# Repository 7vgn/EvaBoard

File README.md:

# EvaBoard evolved
## An Evaluation Board for the ATmega644(A)

This is an evaluation board for the ATmega644(A). It is inspired by (and compatible with) the [evaluation board](https://www.embedded.rwth-aachen.de/doku.php?id=lehre:atmegaevaboard)  used in the lab course "Praktikum Systemprogrammierung" in the computer science curriculum at RWTH Aachen. 

This repository contains:

- A richly illustrated [Guide Book](Guide/EvaBoardGuide.pdf) with everything you need to know to build and use the board
- A [KiCAD project](KiCAD/) with the [Schematic](KiCAD/Schematic.pdf) and a PCB layout, ready to be manufactured
- The [bill of materials](BOM/BOM.pdf)
- Drivers for the [LCD](Drivers/LCD/) and the [serial port](Drivers/Serial/)
- [Test code](Tests/) for testing and debugging the board

Related projects:

- [SRAM Board evolved](https://github.com/7vgn/SRAMBoard/), an add-on board with 128kBytes of additional SRAM
- [AD/DA Board evolved](https://github.com/7vgn/ADDABoard/), an add-on board for experimenting with analogue-digital and digital-analogue conversion

> [!NOTE]
> I have a small number of PCBs left over. If you're a student wanting to build the board, [contact me](https://github.com/7vgn/EvaBoard/discussions).

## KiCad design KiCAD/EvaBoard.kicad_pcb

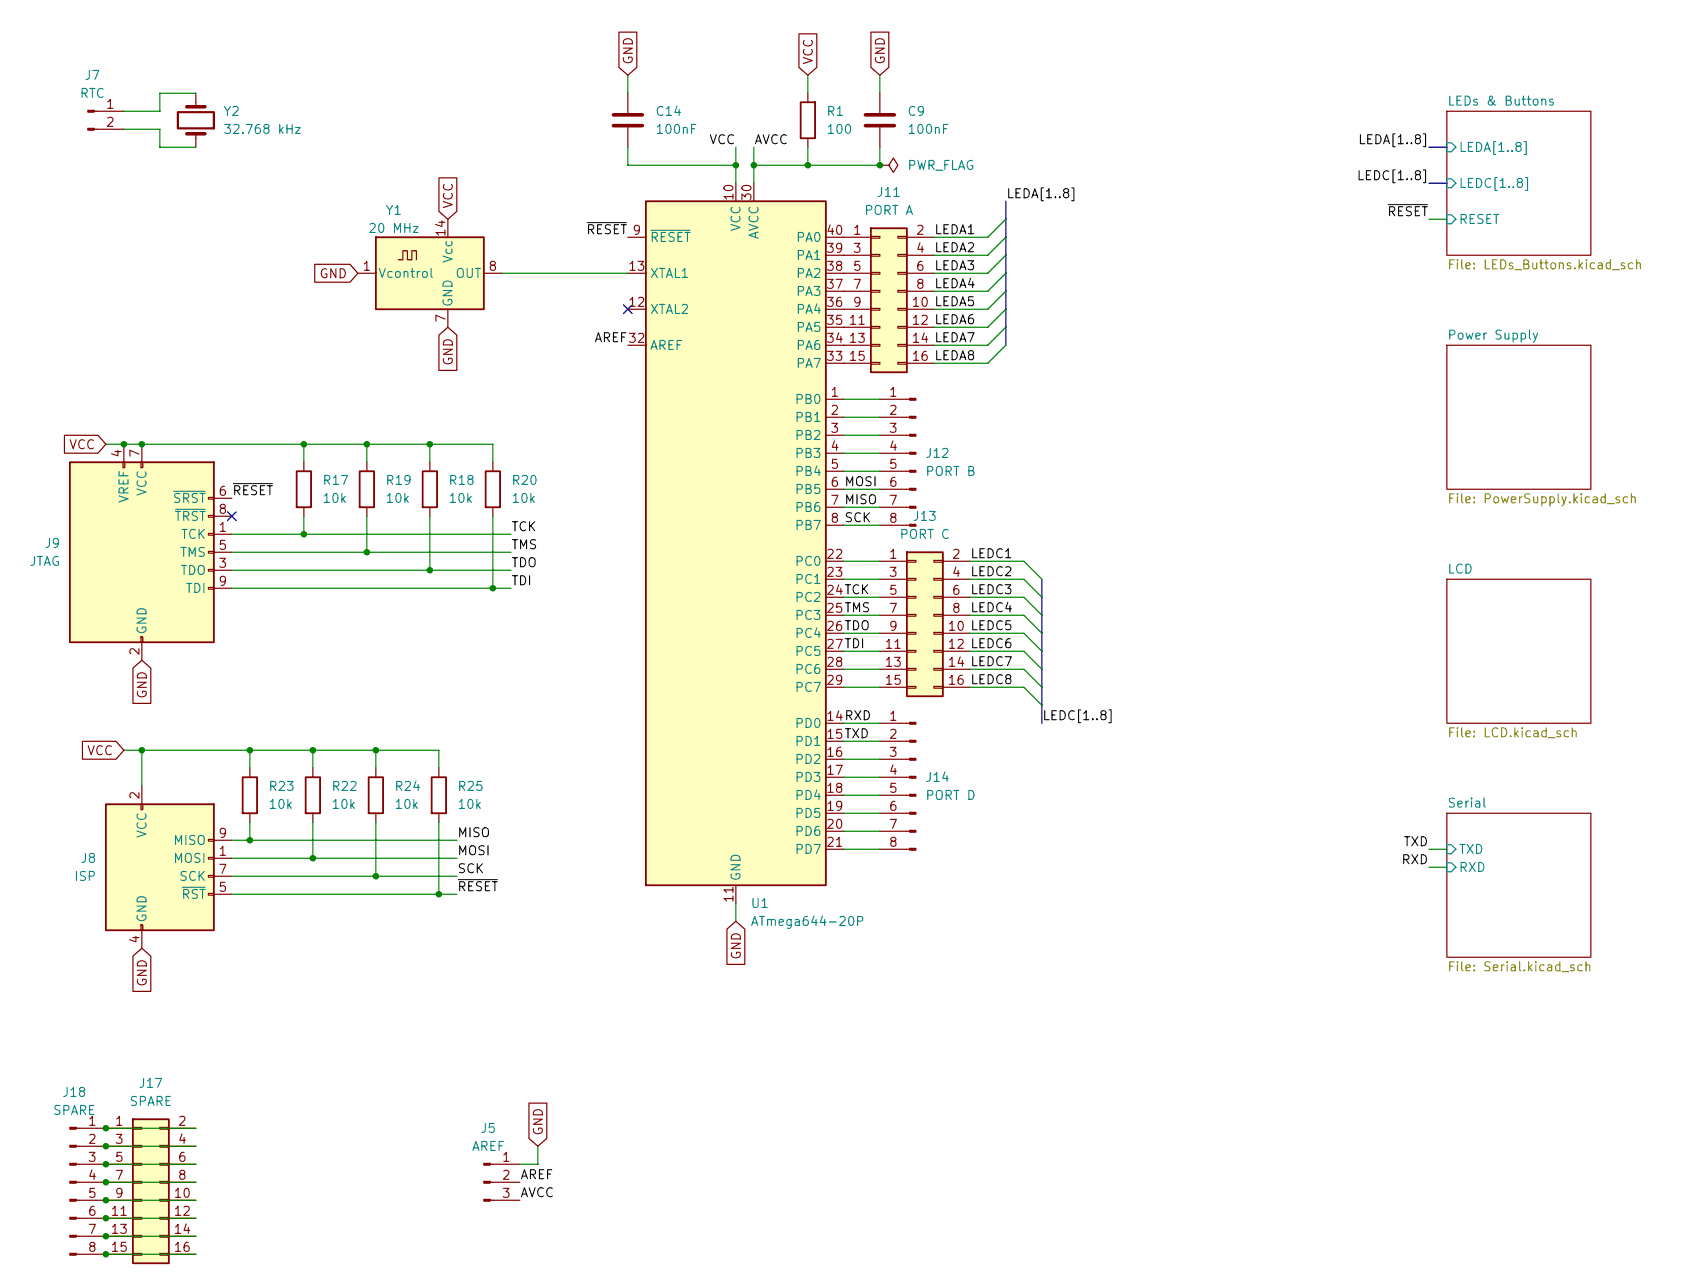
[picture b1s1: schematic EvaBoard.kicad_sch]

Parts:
C9, C14: 100nF; C_Disc_D5.0mm_W2.5mm_P5.00mm
J5: AREF; PinHeader_1x03_P2.54mm_Vertical
J7: RTC; PinHeader_1x02_P2.54mm_Vertical
J8: ISP; IDC-Header_2x05_P2.54mm_Vertical
J9: JTAG; IDC-Header_2x05_P2.54mm_Vertical
J11: PORT A; PinHeader_2x08_P2.54mm_Vertical
J12: PORT B; PinHeader_1x08_P2.54mm_Vertical
J13: PORT C; PinHeader_2x08_P2.54mm_Vertical
J14: PORT D; PinHeader_1x08_P2.54mm_Vertical
J17: SPARE; PinHeader_2x08_P2.54mm_Vertical
J18: SPARE; PinHeader_1x08_P2.54mm_Vertical
R1: 100; R_Axial_DIN0207_L6.3mm_D2.5mm_P10.16mm_Horizontal
R17, R18, R19, R20, R22, R23, R24, R25: 10k; R_Axial_DIN0207_L6.3mm_D2.5mm_P10.16mm_Horizontal
U1: ATmega644-20P; DIP-40_W15.24mm
Y1: 20 MHz; DIP-14_W7.62mm
Y2: 32.768 kHz; Crystal_C38-LF_D3.0mm_L8.0mm_Horizontal

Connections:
/AREF: J5.2, U1.32 (AREF)
/AVCC: C9.1, J5.3, R1.1, U1.30 (AVCC)
/LEDA1: J11.2; also elsewhere on the board
/LEDA2: J11.4; also elsewhere on the board
/LEDA3: J11.6; also elsewhere on the board
/LEDA4: J11.8; also elsewhere on the board
/LEDA5: J11.10; also elsewhere on the board
/LEDA6: J11.12; also elsewhere on the board
/LEDA7: J11.14; also elsewhere on the board
/LEDA8: J11.16; also elsewhere on the board
/LEDC1: J13.2; also elsewhere on the board
/LEDC2: J13.4; also elsewhere on the board
/LEDC3: J13.6; also elsewhere on the board
/LEDC4: J13.8; also elsewhere on the board
/LEDC5: J13.10; also elsewhere on the board
/LEDC6: J13.12; also elsewhere on the board
/LEDC7: J13.14; also elsewhere on the board
/LEDC8: J13.16; also elsewhere on the board
/MISO: J8.9 (MISO), J12.7, R23.2, U1.7 (PB6)
/MOSI: J8.1 (MOSI), J12.6, R22.2, U1.6 (PB5)
/RXD: J14.1, U1.14 (PD0); also elsewhere on the board
/SCK: J8.7 (SCK), J12.8, R24.2, U1.8 (PB7)
/TCK: J9.1 (TCK), J13.5, R17.2, U1.24 (PC2)
/TDI: J9.9 (TDI), J13.11, R20.2, U1.27 (PC5)
/TDO: J9.3 (TDO), J13.9, R18.2, U1.26 (PC4)
/TMS: J9.5 (TMS), J13.7, R19.2, U1.25 (PC3)
/TXD: J14.2, U1.15 (PD1); also elsewhere on the board
/~RESET: J8.5 (~RST), J9.6 (~SRST), R25.2, U1.9 (~RESET); also elsewhere on the board
GND: C9.2, C14.1, J5.1, J8.4 (GND), J8.6 (GND), J8.8 (GND), J8.10 (GND), J9.2 (GND), J9.10 (GND), U1.11 (GND), U1.31 (GND), Y1.1 (Vcontrol), Y1.7 (GND); also elsewhere on the board
unnamed: J7.1, Y2.2
unnamed: J7.2, Y2.1
unnamed: J11.1, U1.40 (PA0)
unnamed: J11.3, U1.39 (PA1)
unnamed: J11.5, U1.38 (PA2)
unnamed: J11.7, U1.37 (PA3)
unnamed: J11.9, U1.36 (PA4)
unnamed: J11.11, U1.35 (PA5)
unnamed: J11.13, U1.34 (PA6)
unnamed: J11.15, U1.33 (PA7)
unnamed: J12.1, U1.1 (PB0)
unnamed: J12.2, U1.2 (PB1)
unnamed: J12.3, U1.3 (PB2)
unnamed: J12.4, U1.4 (PB3)
unnamed: J12.5, U1.5 (PB4)
unnamed: J13.1, U1.22 (PC0)
unnamed: J13.3, U1.23 (PC1)
unnamed: J13.13, U1.28 (PC6)
unnamed: J13.15, U1.29 (PC7)
unnamed: J14.3, U1.16 (PD2)
unnamed: J14.4, U1.17 (PD3)
unnamed: J14.5, U1.18 (PD4)
unnamed: J14.6, U1.19 (PD5)
unnamed: J14.7, U1.20 (PD6)
unnamed: J14.8, U1.21 (PD7)
unnamed: J17.1, J17.2, J18.1
unnamed: J17.3, J17.4, J18.2
unnamed: J17.5, J17.6, J18.3
unnamed: J17.7, J17.8, J18.4
unnamed: J17.9, J17.10, J18.5
unnamed: J17.11, J17.12, J18.6
unnamed: J17.13, J17.14, J18.7
unnamed: J17.15, J17.16, J18.8
unnamed: U1.13 (XTAL1), Y1.8 (OUT)
VCC: C14.2, J8.2 (VCC), J9.4 (VREF), J9.7 (VCC), R1.2, R17.1, R18.1, R19.1, R20.1, R22.1, R23.1, R24.1, R25.1, U1.10 (VCC), Y1.14 (Vcc); also elsewhere on the board

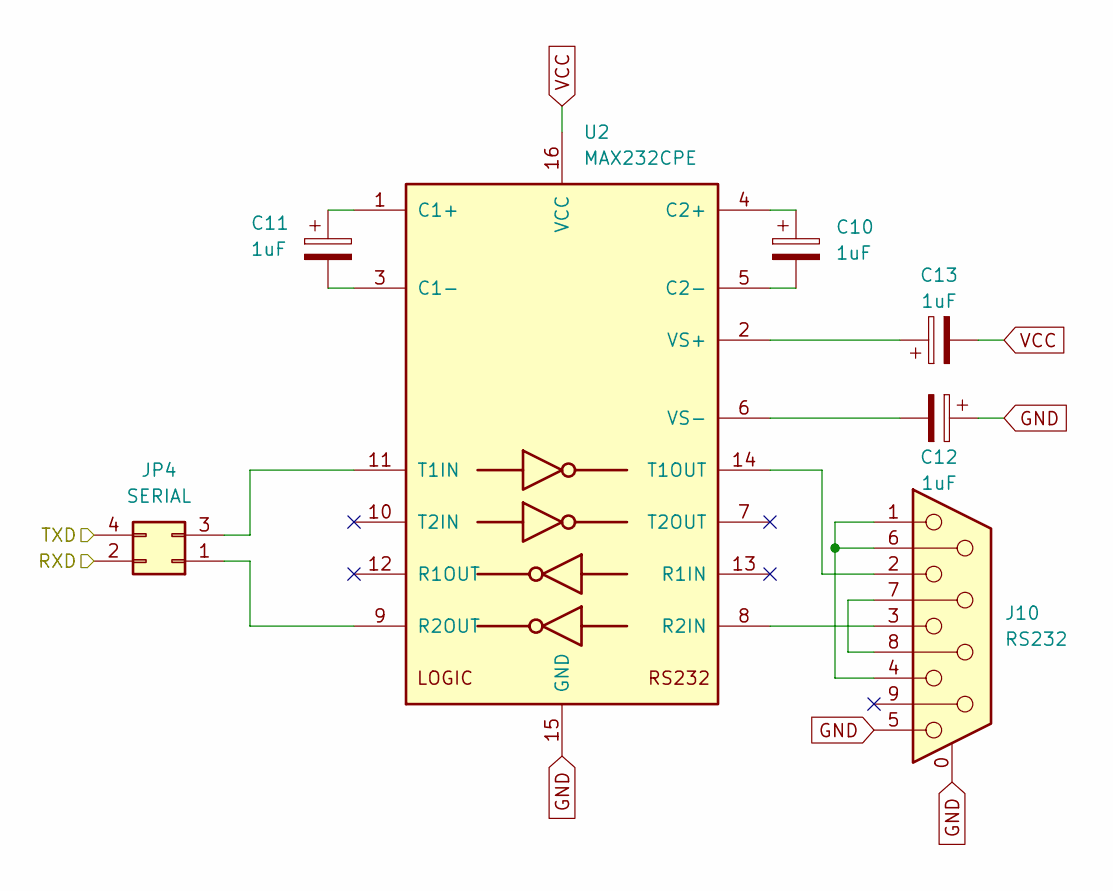
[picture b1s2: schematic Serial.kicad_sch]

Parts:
C10, C11, C12, C13: 1uF; CP_Radial_D5.0mm_P2.00mm
J10: RS232; DSUB-9_Female_Horizontal_P2.77x2.84mm_EdgePinOffset7.70mm_H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
JP4: SERIAL; PinHeader_2x02_P2.54mm_Vertical
U2: MAX232CPE; DIP-16_W7.62mm

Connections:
/RXD: JP4.2; also elsewhere on the board
/TXD: JP4.4; also elsewhere on the board
GND: C12.1, J10.0 (PAD), J10.5, U2.15 (GND); also elsewhere on the board
unnamed: C10.1, U2.4 (C2+)
unnamed: C10.2, U2.5 (C2-)
unnamed: C11.1, U2.1 (C1+)
unnamed: C11.2, U2.3 (C1-)
unnamed: C12.2, U2.6 (VS-)
unnamed: C13.1, U2.2 (VS+)
unnamed: J10.1, J10.4, J10.6
unnamed: J10.2, U2.14 (T1OUT)
unnamed: J10.3, U2.8 (R2IN)
unnamed: J10.7, J10.8
unnamed: JP4.1, U2.9 (R2OUT)
unnamed: JP4.3, U2.11 (T1IN)
VCC: C13.2, U2.16 (VCC); also elsewhere on the board

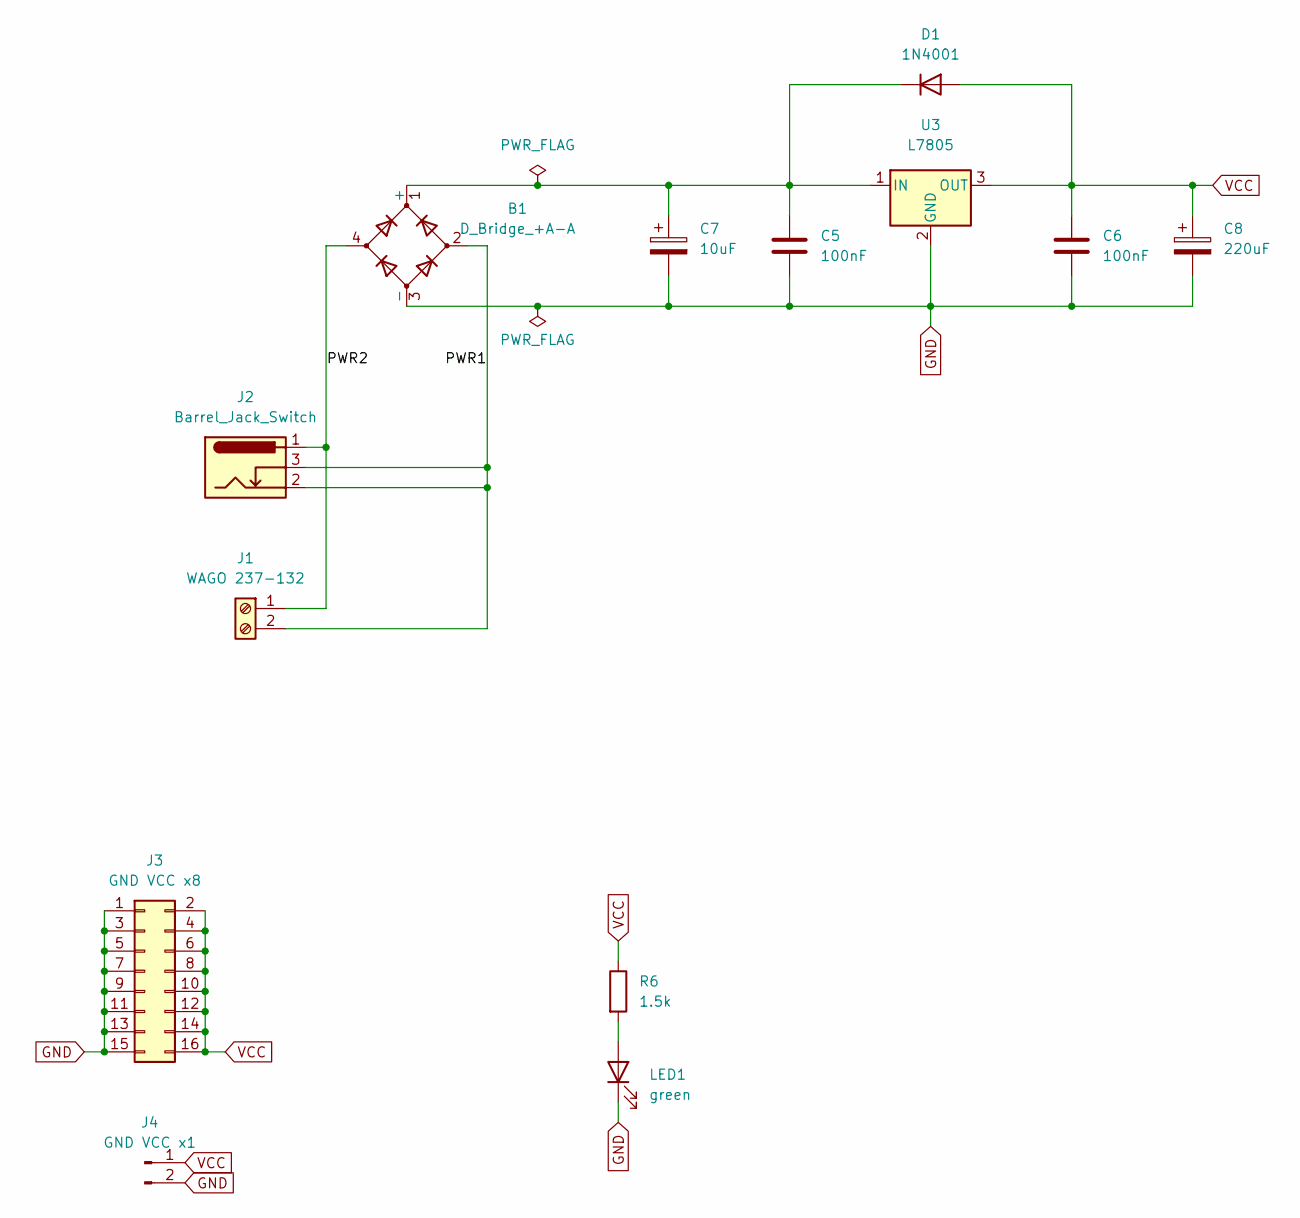
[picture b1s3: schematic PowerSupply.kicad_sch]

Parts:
B1: D_Bridge_+A-A; Diode_Bridge_Round_D8.9mm
C5, C6: 100nF; C_Disc_D5.0mm_W2.5mm_P5.00mm
C7: 10uF; CP_Axial_L18.0mm_D6.5mm_P25.00mm_Horizontal
C8: 220uF; CP_Radial_D10.0mm_P5.00mm
D1: 1N4001; D_DO-41_SOD81_P10.16mm_Horizontal
J1: WAGO 237-132; TerminalBlock_RND_205-00001_1x02_P5.00mm_Horizontal
J2: Barrel_Jack_Switch; BarrelJack_Horizontal
J3: GND VCC x8; PinHeader_2x08_P2.54mm_Vertical
J4: GND VCC x1; PinHeader_1x02_P2.54mm_Vertical
LED1: green; LED_D3.0mm
R6: 1.5k; R_Axial_DIN0207_L6.3mm_D2.5mm_P10.16mm_Horizontal
U3: L7805; TO-220-3_Horizontal_TabDown

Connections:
/Power Supply/PWR1: B1.2, J1.2, J2.2, J2.3
/Power Supply/PWR2: B1.4, J1.1, J2.1
GND: B1.3 (-), C5.2, C6.2, C7.2, C8.2, J3.1, J3.3, J3.5, J3.7, J3.9, J3.11, J3.13, J3.15, J4.2, LED1.1 (K), U3.2 (GND); also elsewhere on the board
unnamed: B1.1 (+), C5.1, C7.1, D1.1 (K), U3.1 (IN)
unnamed: LED1.2 (A), R6.2
VCC: C6.1, C8.1, D1.2 (A), J3.2, J3.4, J3.6, J3.8, J3.10, J3.12, J3.14, J3.16, J4.1, R6.1, U3.3 (OUT); also elsewhere on the board

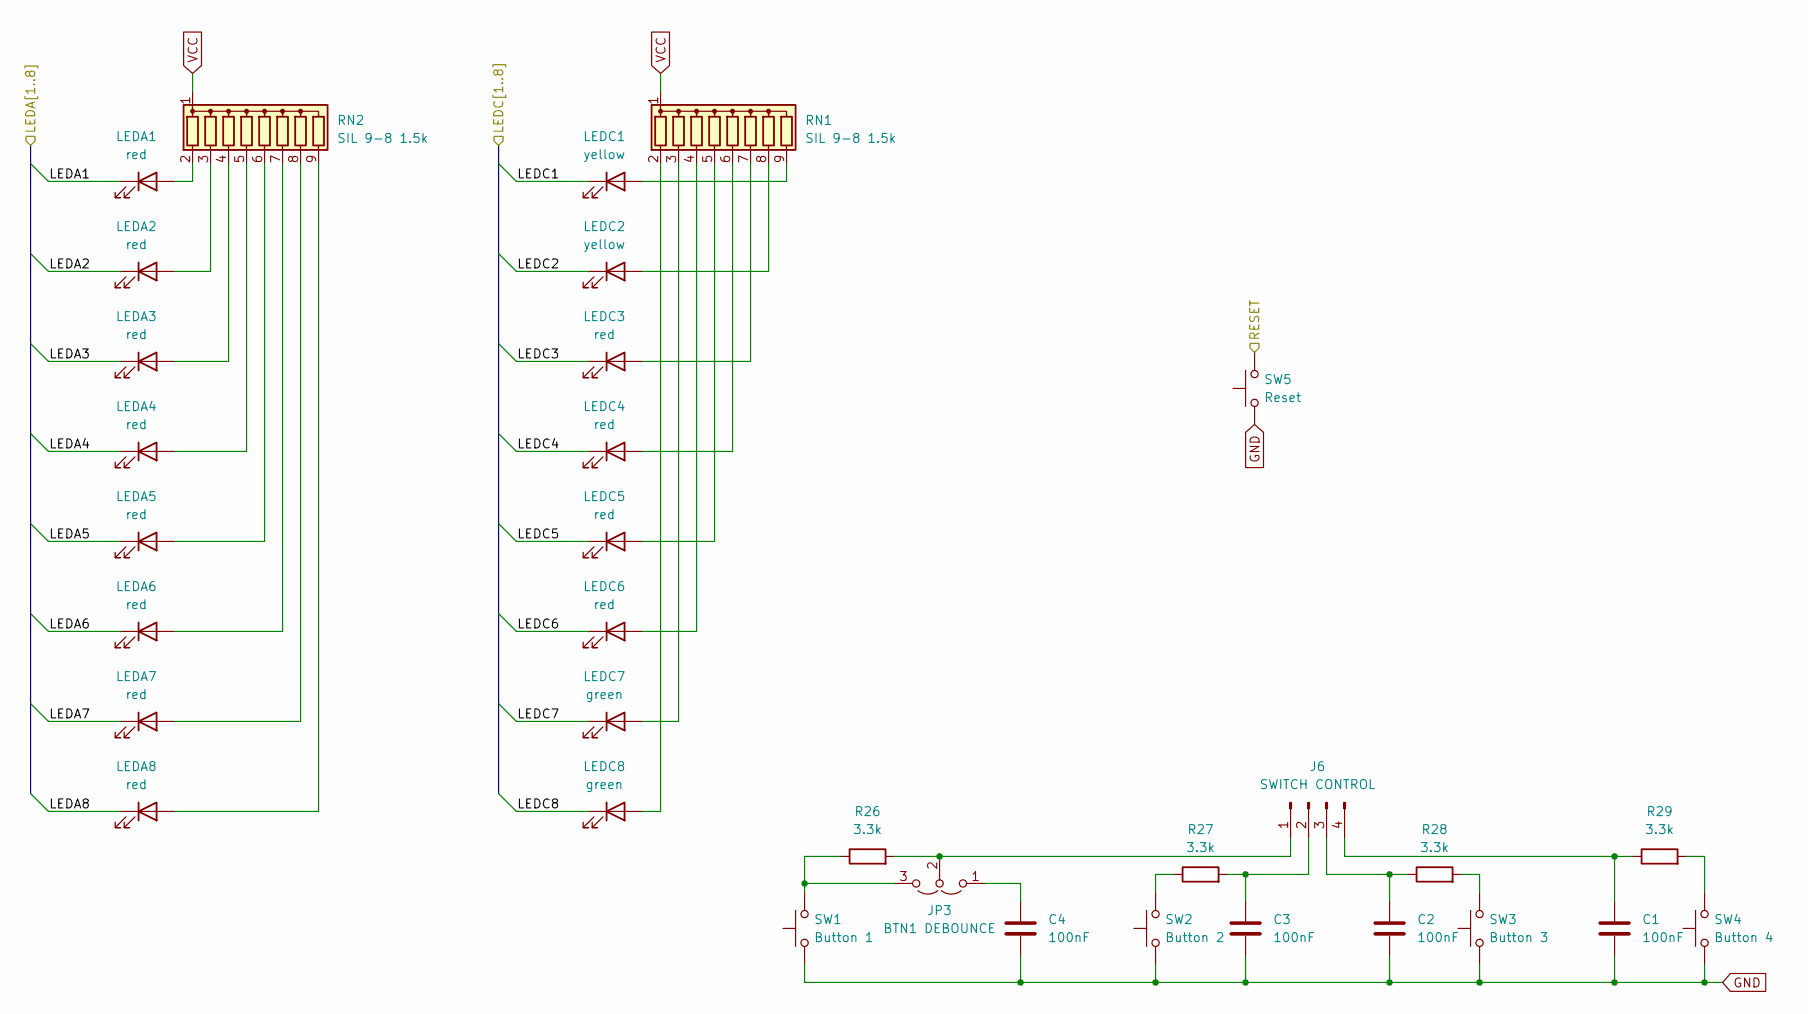
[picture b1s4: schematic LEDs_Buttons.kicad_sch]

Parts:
C1, C2, C3, C4: 100nF; C_Disc_D5.0mm_W2.5mm_P5.00mm
J6: SWITCH CONTROL; PinHeader_1x04_P2.54mm_Vertical
JP3: BTN1 DEBOUNCE; PinHeader_1x03_P2.54mm_Vertical
LEDA1, LEDA2, LEDA3, LEDA4, LEDA5, LEDA6, LEDA7, LEDA8: red; LED_D3.0mm
LEDC1, LEDC2: yellow; LED_D3.0mm
LEDC3, LEDC4, LEDC5, LEDC6: red; LED_D3.0mm
LEDC7, LEDC8: green; LED_D3.0mm
R26, R27, R28, R29: 3.3k; R_Axial_DIN0207_L6.3mm_D2.5mm_P10.16mm_Horizontal
RN1, RN2: SIL 9-8 1.5k; R_Array_SIP9
SW1: Button 1; SW_PUSH_6mm
SW2: Button 2; SW_PUSH_6mm
SW3: Button 3; SW_PUSH_6mm
SW4: Button 4; SW_PUSH_6mm
SW5: Reset; SW_PUSH_6mm

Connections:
/LEDA1: LEDA1.1 (K); also elsewhere on the board
/LEDA2: LEDA2.1 (K); also elsewhere on the board
/LEDA3: LEDA3.1 (K); also elsewhere on the board
/LEDA4: LEDA4.1 (K); also elsewhere on the board
/LEDA5: LEDA5.1 (K); also elsewhere on the board
/LEDA6: LEDA6.1 (K); also elsewhere on the board
/LEDA7: LEDA7.1 (K); also elsewhere on the board
/LEDA8: LEDA8.1 (K); also elsewhere on the board
/LEDC1: LEDC1.1 (K); also elsewhere on the board
/LEDC2: LEDC2.1 (K); also elsewhere on the board
/LEDC3: LEDC3.1 (K); also elsewhere on the board
/LEDC4: LEDC4.1 (K); also elsewhere on the board
/LEDC5: LEDC5.1 (K); also elsewhere on the board
/LEDC6: LEDC6.1 (K); also elsewhere on the board
/LEDC7: LEDC7.1 (K); also elsewhere on the board
/LEDC8: LEDC8.1 (K); also elsewhere on the board
/~RESET: SW5.2; also elsewhere on the board
GND: C1.1, C2.1, C3.1, C4.2, SW1.1, SW2.1, SW3.1, SW4.1, SW5.1; also elsewhere on the board
unnamed: C1.2, J6.4, R29.1
unnamed: C2.2, J6.3, R28.1
unnamed: C3.2, J6.2, R27.2
unnamed: C4.1, JP3.1 (A)
unnamed: J6.1, JP3.2 (C), R26.2
unnamed: JP3.3 (B), R26.1, SW1.2
unnamed: LEDA1.2 (A), RN2.2 (R1)
unnamed: LEDA2.2 (A), RN2.3 (R2)
unnamed: LEDA3.2 (A), RN2.4 (R3)
unnamed: LEDA4.2 (A), RN2.5 (R4)
unnamed: LEDA5.2 (A), RN2.6 (R5)
unnamed: LEDA6.2 (A), RN2.7 (R6)
unnamed: LEDA7.2 (A), RN2.8 (R7)
unnamed: LEDA8.2 (A), RN2.9 (R8)
unnamed: LEDC1.2 (A), RN1.9 (R8)
unnamed: LEDC2.2 (A), RN1.8 (R7)
unnamed: LEDC3.2 (A), RN1.7 (R6)
unnamed: LEDC4.2 (A), RN1.6 (R5)
unnamed: LEDC5.2 (A), RN1.5 (R4)
unnamed: LEDC6.2 (A), RN1.4 (R3)
unnamed: LEDC7.2 (A), RN1.3 (R2)
unnamed: LEDC8.2 (A), RN1.2 (R1)
unnamed: R27.1, SW2.2
unnamed: R28.2, SW3.2
unnamed: R29.2, SW4.2
VCC: RN1.1 (common), RN2.1 (common); also elsewhere on the board

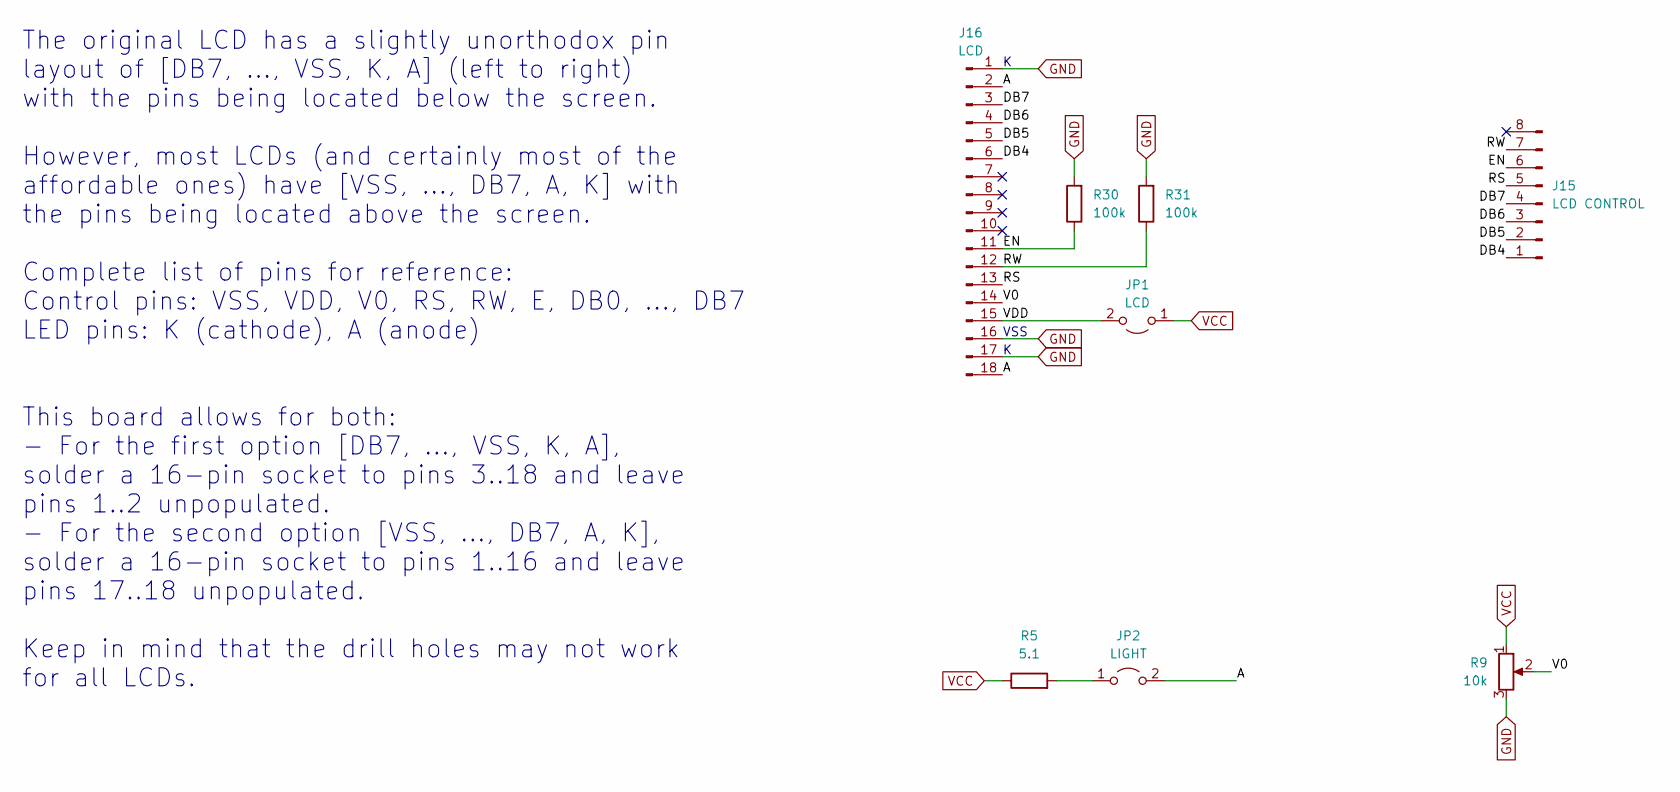
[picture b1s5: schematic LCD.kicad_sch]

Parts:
J15: LCD CONTROL; PinHeader_1x08_P2.54mm_Vertical
J16: LCD; PinSocket_1x18_P2.54mm_Vertical
JP1: LCD; PinHeader_1x02_P2.54mm_Vertical
JP2: LIGHT; PinHeader_1x02_P2.54mm_Vertical
R5: 5.1; R_Axial_DIN0207_L6.3mm_D2.5mm_P10.16mm_Horizontal
R9: 10k; Potentiometer_Bourns_3386P_Vertical
R30, R31: 100k; R_Axial_DIN0207_L6.3mm_D2.5mm_P10.16mm_Horizontal

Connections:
/LCD/A: J16.2, J16.18, JP2.2 (B)
/LCD/DB4: J15.1, J16.6
/LCD/DB5: J15.2, J16.5
/LCD/DB6: J15.3, J16.4
/LCD/DB7: J15.4, J16.3
/LCD/EN: J15.6, J16.11, R30.1
/LCD/RS: J15.5, J16.13
/LCD/RW: J15.7, J16.12, R31.1
/LCD/V0: J16.14, R9.2
/LCD/VDD: J16.15, JP1.2 (B)
GND: J16.1, J16.16, J16.17, R9.3, R30.2, R31.2; also elsewhere on the board
unnamed: JP2.1 (A), R5.2
VCC: JP1.1 (A), R5.1, R9.1; also elsewhere on the board

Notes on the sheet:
The original LCD has a slightly unorthodox pin layout of [DB7, ..., VSS, K, A] (left to right) with the pins being located below the screen. However, most LCDs (and certainly most of the affordable ones) have [VSS, ..., DB7, A, K] with the pins being located above the screen. Complete list of pins 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
VSS

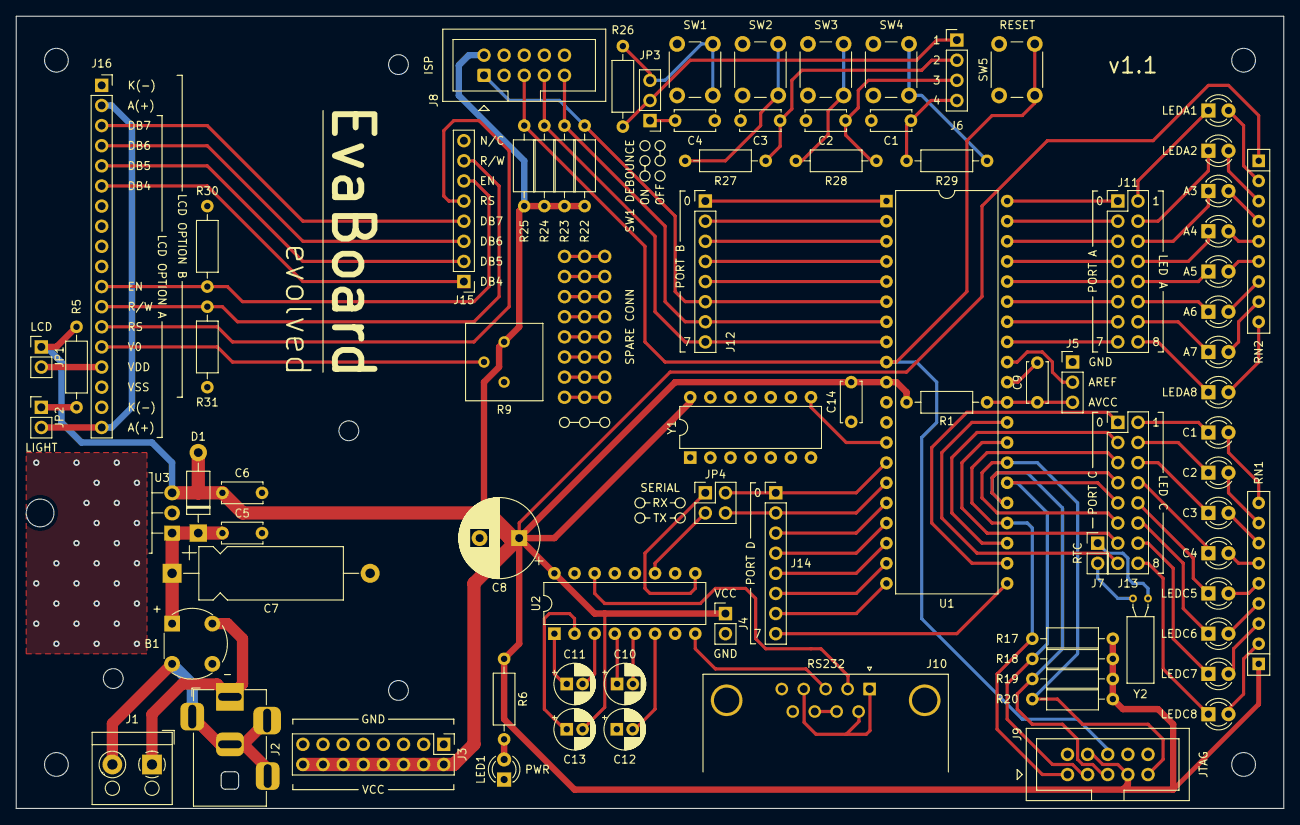
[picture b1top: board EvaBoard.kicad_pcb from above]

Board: 2 copper layers, 160.0 x 100.0 mm, 85 parts (0 on the bottom side), 116 nets.

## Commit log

2024-02-29 Typos
2024-02-29 Fixed typos
2024-03-04 Added pics in Programming section
2025-10-03 Clarifications in Chapter 3 after student feedback
